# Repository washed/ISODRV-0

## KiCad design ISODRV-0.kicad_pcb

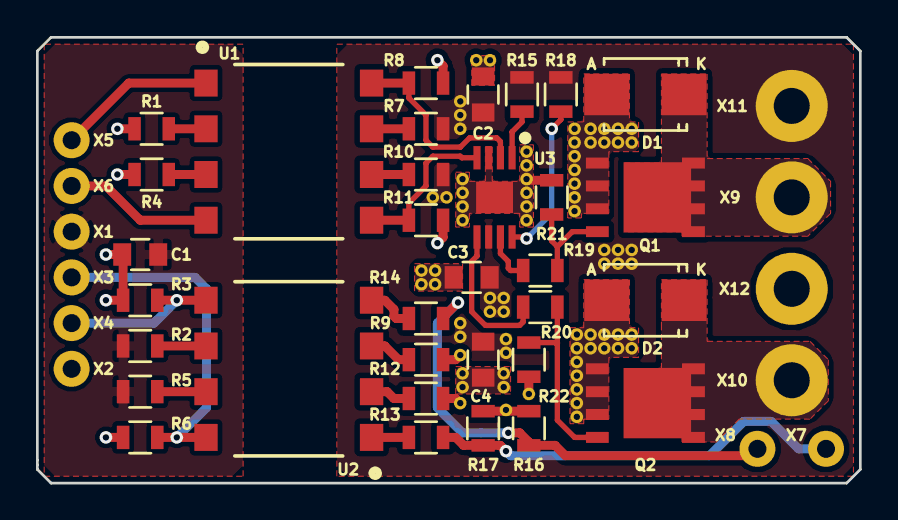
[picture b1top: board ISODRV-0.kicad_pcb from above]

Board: 2 copper layers, 45.7 x 24.8 mm, 45 parts (0 on the bottom side), 30 nets.

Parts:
C1, C2, C3: 100n 50V; C_0805
C4: 1µ 50V; C_0805
D1, D2: B360B-FDICT; SMB
Q1, Q2: FDMS7660ASCT; Power56
R1, R4: 470R; R_0805
R2, R5, R7, R10, R13, R14: 0R; R_0805
R3, R6, R8, R11: 1k; R_0805
R9, R12: 1k8; R_0805
R15, R16, R17, R18: 10k; R_0805
R19: 0R | 10R; R_0805
R20: 0 | 10R; R_0805
R21, R22: DNI; R_0805
U1, U2: MCT62SDCT; SMT-8 MCT6
U3: 2EDN8524R; PG-TSSOP-8
X1, X2, X3, X4, X5, X6, X7, X8: wirepad; THTPAD-1x2
X9, X10, X11, X12: wirepad; THTPAD-2x4

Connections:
GNDA: C2.2, C3.2, C4.2, D1.2, D2.2, Q1.1, Q1.2, Q1.3, Q2.1, Q2.2, Q2.3, R8.1, R9.2, R11.1, R12.2, R16.2, R17.2, R21.1, R22.1, U3.3, U3.9, X12.1
GNDD: C1.2, R1.1, R3.2, R4.1, R6.2, X2.1
M1: D1.1, Q1.5, Q1.6, Q1.7, Q1.8, Q1.PAD, X9.1
M2: D2.1, Q2.5, Q2.6, Q2.7, Q2.8, Q2.PAD, X10.1
unnamed: Q1.4, R19.1, R21.2
unnamed: Q2.4, R20.1, R22.2
unnamed: R1.2, U1.2
unnamed: R2.2, U2.6
unnamed: R4.2, U1.3
unnamed: R5.2, U2.7
unnamed: R7.1, U1.7
unnamed: R8.2, U1.8, U3.2
unnamed: R9.1, U2.3
unnamed: R10.1, U1.6
unnamed: R11.2, U1.5, U3.4
unnamed: R12.1, U2.2
unnamed: R13.1, U2.1
unnamed: R14.1, U2.4
unnamed: R15.2, U3.1
unnamed: R18.2, U3.8
unnamed: R19.2, U3.7
unnamed: R20.2, U3.5
ONA: U1.1, X5.1
ONB: U1.4, X6.1
OUTA: R6.1, U2.8, X3.1
OUTB: R3.1, U2.5, X4.1
T1: R13.2, R17.1, X7.1
T2: R14.2, R16.1, X8.1
VAA: C2.1, C3.1, C4.1, R7.2, R10.2, R15.1, R18.1, U3.6, X11.1
VDD: C1.1, R2.1, R5.1, X1.1

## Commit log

2017-03-07 Add .gitignore
